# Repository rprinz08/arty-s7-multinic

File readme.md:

# Arty-S7-50, VexRiscV, Migen, LiteX, MulitNet

This project describes how to build a soft-core RiscV based system with multiple
Ethernet interfaces on a Digilent Arty-S7-50 with a Xilinx Spartan 7 FPGA using
Python based Migen HDL and LiteX SoC builder.

Prototype of the project

More evolved version with up to four Ethernet interfaces and a PCB. The [KiCad](https://kicad-pcb.org/) project files are included in this repository.

Download schematic as [PDF](doc/arty_s7_50_multi_net_sch.pdf).

It uses multiple [Texas Instruments DP83848](http://www.ti.com/product/DP83848-EP)
based RMII Ethernet PHYs from [Waveshare](https://www.waveshare.com/dp83848-ethernet-board.htm).
In addition a [SD-Card PMOD](https://store.digilentinc.com/pmod-microsd-microsd-card-slot/) completes the system.

Note: in the PCB version the Seven Segment Display was removed due to I/O limitations.

More infos about this project can be found in the accompanying blog posts
[here](https://www.min.at/prinz/?x=entry:entry200428-150015) and [here](https://www.min.at/prinz/?x=entry:entry200602-105212).

## Prerequisites

To build the FPGA bitstream, the SoC BIOS and the sample bare metal demo
application you need some prerequisites installed:

* [Xilinx Vivado](https://www.xilinx.com/products/design-tools/vivado.html)
* [Python >= 3.6](https://www.python.org/)
* [LiteX](https://github.com/enjoy-digital/litex)
  * Tested with git version (bddb170)
* [Liteeth](https://github.com/enjoy-digital/liteeth)
  * Tested with git version (dea3590)
* [RiscV compiler toolchain](https://static.dev.sifive.com/dev-tools/riscv64-unknown-elf-gcc-8.1.0-2019.01.0-x86_64-linux-ubuntu14.tar.gz)
* [OpenOCD](http://openocd.org/)
* [xc3sprog](https://sourceforge.net/projects/xc3sprog/) (optional)

*Note: As of LiteX version (bddb170) and Liteeth version (dea3590) no patches are needed for multiple ethernet support. If you use an older version you can find patches in the history.*

## Building

The included `make.py` script is responsible for building and loading/flashing.
In addition a `Makefile` is used to handle dependencies and file changes.
Assuming that all prerequisites are correctly installed using make:
```
make                Builds FPGA bitstream and BIOS software
make build-sw       Builds BIOS
make build-fpga     Builds FPGA bitstream
make conv           Convert Python FHDL to Verilog
make load           Loads bitstream into FPGA via serial port
make load-sw        Loads firmware binary using serial port
make reload         Same as "load" but does not rebuild in case of changes
make flash          Stores bitstream into FPGA boot flash
make flash-sw       Flash BIOS software
make reflash        Same as "flash" but does not rebuild in case of changes
make term           Opens LiteX serial lxterm console
make clean          Cleans/removes all build artefacts
```
The `make.py` script is called from make (Makefile) and provides the following:
```
make.py --help      shows basic help
make.py build       converts LiteX/Migen FHDL into verilog,
                    starts Xilinx Vivado and generates FPGA bitstream
make.py build-sw    same as 'build' but only builds BIOS
make.py build-fpga  same as 'build' but only builds FPGA bitstream
make.py load        loads the bitstream into FPGA
make.py flash       flashes the bitstream into config flash
make.py flash-sw    flashes the BIOS into config flash
make.py conv        creates all artefacts (verilog, c sources etc.)
                    but does not compile
```
In addition to the FPGA bitstream (which also includes the BIOS) a sample
application is included in the `firmware` directory. It can be compiled with
the included Makefile. The resulting `firmware.bin` can be loaded from SD-Card
or via TFTP from a server.

To load from SD-Card create a FAT16 partition on it and place `firmware.bin`
renamed to `boot.bin` in the root directory.

To load from TFTP server connect Ethernet interface 1 to a switch or directly
to a host via a cros-over network cable. Interface 1 is per default configured
with IP4 address **10.0.0.50** and tries to load from TFTP server with address
**10.0.0.100**. These addresses are static and can only be changed by modifying
`top.py` and re-building.
Place `firmware.bin` renamed to `BOOT.BIN` in the root directory of the TFTP
server.

To preserve the limited I/Os of the Arty the SD-Card can be removed and the
firmware booted from the SPI flash. The Arty has 16MB SPI flash normally used
to configure the FPGA with a bitstream at boot.
As lang as bitstream size + firmware size < 15MB they can reside together in
the flash. Current configuration halfs the flash. First half used for the
bitsream second half for the firmware. The `make flash-sw` writes the
`firmware.fbi` to flash adress 0x800000.

*Note: Due to BIOS ROM size limitations the option to boot from SPI flash has been disabled. Booting the system is possible via SPI SD-Card, TFTP and serial.*

## Running

Build and flash the FPGA bitstream:
```
make
make flash
```
To boot from SD-Card place `firmware.bin` renamed to `BOOT.BIN` on SD-Card and
reset the board. To boot from SPI flash, flash with `make flash-sw`.
On an attached serial terminal (open one with `make term`) you should see the
following output:
```
[LXTERM] Starting...
        __   _ __      _  __
       / /  (_) /____ | |/_/
      / /__/ / __/ -_)>  <
     /____/_/\__/\__/_/|_|
   Build your hardware, easily!

 (c) Copyright 2012-2020 Enjoy-Digital
 (c) Copyright 2007-2015 M-Labs

 BIOS built on May  1 2020 22:04:43
 BIOS CRC passed (f662f7bd)

 Migen git sha1: --------
 LiteX git sha1: 56aa7897

--=============== SoC ==================--
CPU:       VexRiscv @ 100MHz
ROM:       32KB
SRAM:      4KB
L2:        8KB
MAIN-RAM:  262144KB

--========== Initialization ============--
Ethernet init...
Initializing SDRAM...
SDRAM now under software control
Read leveling:
m0, b0: |00000000000000000000000000000000| delays: -
m0, b1: |00000000000000000000000000000000| delays: -
m0, b2: |00000000000000000000000000000000| delays: -
m0, b3: |00000000000000000000000000000000| delays: -
m0, b4: |00000000000000000000000000000000| delays: -
m0, b5: |00000000000000000000000000000000| delays: -
m0, b6: |00001111111111111000000000000000| delays: 10+-06
m0, b7: |00000000000000000000000000000000| delays: -
best: m0, b6 delays: 10+-06
m1, b0: |00000000000000000000000000000000| delays: -
m1, b1: |00000000000000000000000000000000| delays: -
m1, b2: |00000000000000000000000000000000| delays: -
m1, b3: |00000000000000000000000000000000| delays: -
m1, b4: |00000000000000000000000000000000| delays: -
m1, b5: |10000000000000000000000000000000| delays: 00+-00
m1, b6: |00001111111111111000000000000000| delays: 10+-06
m1, b7: |00000000000000000000000000000000| delays: -
best: m1, b6 delays: 10+-06
SDRAM now under hardware control
Memtest OK
Memspeed Writes: 262Mbps Reads: 327Mbps

--============== Boot ==================--
Booting from serial...
Press Q or ESC to abort boot completely.
sL5DdSMmkekro
Timeout
SD Card via SPI Initialising
Reading MBR
Partition 1 Information: Active=0x00, Type=0x06, LBAStart=0x00000800
Partition 1 is FAT16

Read FAT16 Boot Sector
  Jump Code:              0xeb 0x3c 0x90
  OEM Code:               [mkfs.fat]
  Sector Size:            512
  Sectors Per Cluster:    128
  Reserved Sectors:       128
  Number of Fats:         2
  Root Dir Entries:       2048
  Total Sectors Short:    0
  Media Descriptor:       0xf8
  Fat Size Sectors:       128
  Sectors Per Track:      32
  Number of Heads:        64
  Hidden Sectors:         2048
  Total Sectors Long:     4194304
  Drive Number:           0x80
  Current Head:           0x01
  Boot Signature:         0x29
  Volume ID:              0x3fab9b48
  Volume Label:           [LITEX      ]
  Volume Label:           [FAT16   ]
  Boot Sector Signature:  0xaa55

Reclocking from 400KHz to 14285KHz

sdCardFatTable = 0x4fff0000  Reading Fat16 Table (128 Sectors Long)

sdCardFat16RootDir = 0x4ffe0000  Reading Root Directory (128 Sectors Long)

Root Directory
  File 1 [BOOT    .BIN] @ Cluster 3 for 9532 bytes

Reading File [BOOT.BIN] into 0x40000000 : File starts at Cluster 3 length 9532
Clusters: 3

Executing booted program at 0x40000000

--============= Liftoff! ===============--
Hello firmware booting...

HELLO>
```

## Debugging

A [Litescope](https://github.com/enjoy-digital/litescope) debugger is available via eth2 with configured IP address of **10.0.0.42**. The `debug` directory contains some scripts and samples on how to use it.

## Firmware

After board reset the embedded BIOS is started which performs some basic
initalization and then tries to load the firmware via available peripherals.
In this case first via serial port, then via SD-Card and last via Ethernet.
It found the BOOT.BIN `hello` firmware on the SD-Card and loads it.

```
HELLO >help

Available commands:
hello value      - Returns value xor'ed with 0xff in FPGA
time             - show current clock ticks
uptime           - show system uptime in seconds
random [runs]    - show random number generator values, default [500] runs
malloc [runs]    - test UMM malloc, default [500] runs
ping             - ping host (10.0.0.100) via network interface (eth0)
reboot           - reboot CPU
help             - this command
```

The `hello` firmware just shows how to develop bare metal applications using
console in- and output and accessing FPGA logic blocks. Details about the firmware can be found [here](doc/firmware.md).

## RMII notes

Although there exists a OSCIN pin on the DP83848 PHY module which
suggests a clock input, it is the output of the 50MHz oscillator
available on the module. This oscillator directly clocks the DP83848
PHY and is available on the module connector as reference clock
output.

The default LiteX Liteeth RMII MAC operates with the clock of a 50MHz
PLL it instantiates assuming that it must provide the clock to the
PHY. As the PHY modules use their own oscillator the corresponding clock pads are set to Null in the code so that the external clock will be used.

To synchronize the MAC with the PHY the PHYs clock can be
used as input to the MAC instead of the default 50MHz PLL clock
output. 

On Xilinx Spartan7 FPGAs only the positive (P) version of clock
capable (CC) pins can be used as they are internally special wired
and there is only a limited number per I/O bank available.
As each module has its own oscillator they should be synced to its
corresponding MAC. This is somehow inefficient as normally multiple PHYs and
MACs share a common clock. But to prevent modifying each module, each modules
OSCIN is connected to one of four CC-P pin on
the FPGA syncing its corresponding MAC.

Although a simple modification on the module makes it possible to
share clocks. Removing the 0 Ohm resistor R1 makes it possible to clock the
modules from outside via the OSCIN pin.

More infos about this project can be found in the accompanying blog posts
[here](https://www.min.at/prinz/?x=entry:entry200428-150015) and [here](https://www.min.at/prinz/?x=entry:entry200602-105212).

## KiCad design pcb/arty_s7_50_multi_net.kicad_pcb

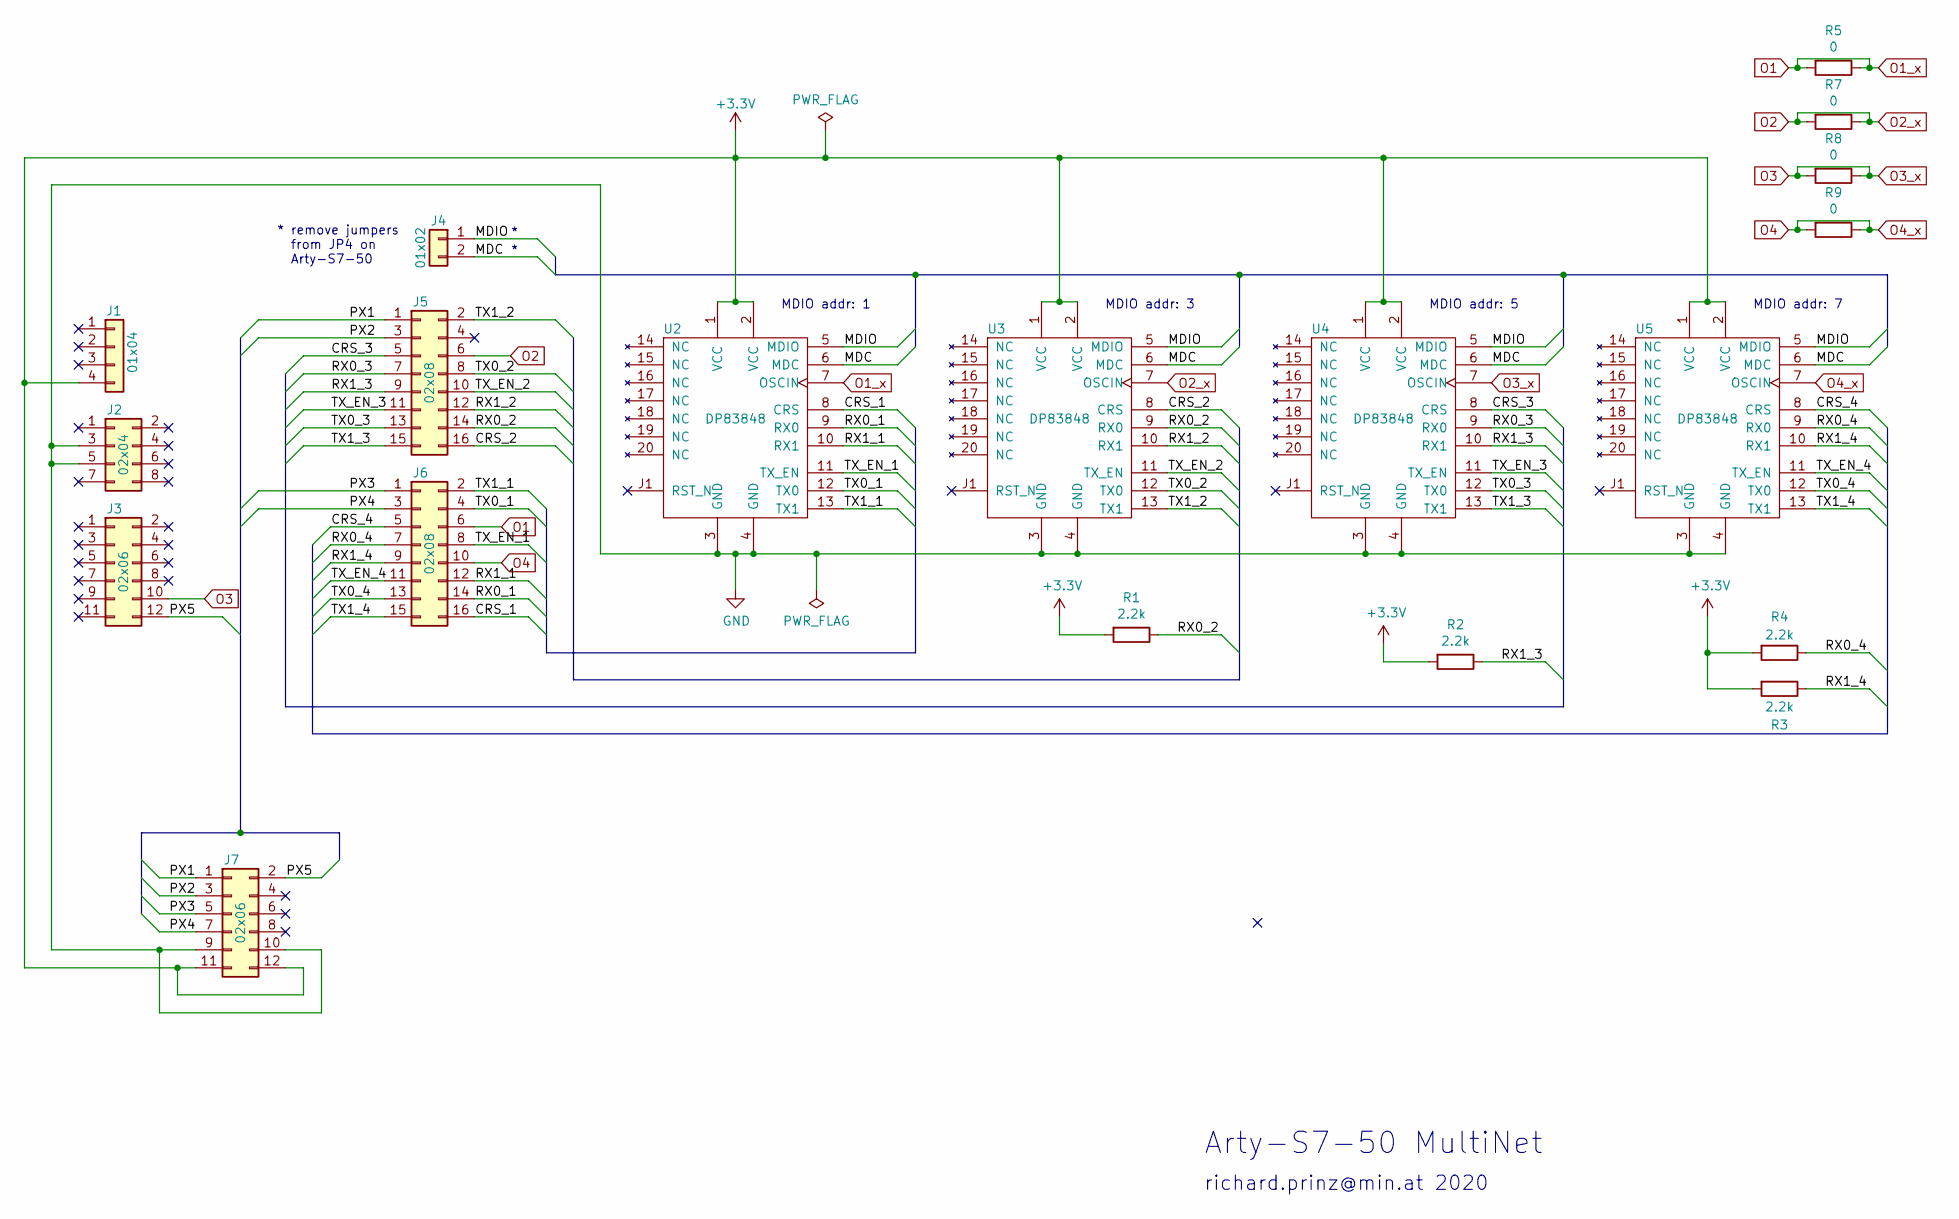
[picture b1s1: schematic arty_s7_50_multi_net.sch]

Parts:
J1: 01x04; Pin_Header_Straight_1x04_Pitch2.54mm
J2: 02x04; Pin_Header_Straight_2x04_Pitch2.54mm
J3, J7: 02x06; Pin_Header_Straight_2x06_Pitch2.54mm
J4: 01x02; Pin_Header_Straight_1x02_Pitch2.54mm
J5, J6: 02x08; Pin_Header_Straight_2x08_Pitch2.54mm
R1, R2, R3, R4: 2.2k; R_0805_HandSoldering
R5, R7, R8, R9: 0; R_0805_HandSoldering
U2, U3, U4, U5: DP83848; Socket_Strip_Straight_2x10_Pitch2.54mm

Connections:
+3V3: J1.4, J7.11, J7.12, R1.2, R2.2, R3.2, R4.2, U2.1 (VCC), U2.2 (VCC), U3.1 (VCC), U3.2 (VCC), U4.1 (VCC), U4.2 (VCC), U5.1 (VCC), U5.2 (VCC)
/CRS_1: J6.16, U2.8 (CRS)
/CRS_2: J5.16, U3.8 (CRS)
/CRS_3: J5.5, U4.8 (CRS)
/CRS_4: J6.5, U5.8 (CRS)
/MDC: J4.2, U2.6 (MDC), U3.6 (MDC), U4.6 (MDC), U5.6 (MDC)
/MDIO: J4.1, U2.5 (MDIO), U3.5 (MDIO), U4.5 (MDIO), U5.5 (MDIO)
/PX1: J5.1, J7.1
/PX2: J5.3, J7.3
/PX3: J6.1, J7.5
/PX4: J6.3, J7.7
/PX5: J3.12, J7.2
/RX0_1: J6.14, U2.9 (RX0)
/RX0_2: J5.14, R1.1, U3.9 (RX0)
/RX0_3: J5.7, U4.9 (RX0)
/RX0_4: J6.7, R4.1, U5.9 (RX0)
/RX1_1: J6.12, U2.10 (RX1)
/RX1_2: J5.12, U3.10 (RX1)
/RX1_3: J5.9, R2.1, U4.10 (RX1)
/RX1_4: J6.9, R3.1, U5.10 (RX1)
/TX0_1: J6.4, U2.12 (TX0)
/TX0_2: J5.8, U3.12 (TX0)
/TX0_3: J5.13, U4.12 (TX0)
/TX0_4: J6.13, U5.12 (TX0)
/TX1_1: J6.2, U2.13 (TX1)
/TX1_2: J5.2, U3.13 (TX1)
/TX1_3: J5.15, U4.13 (TX1)
/TX1_4: J6.15, U5.13 (TX1)
/TX_EN_1: J6.8, U2.11 (TX_EN)
/TX_EN_2: J5.10, U3.11 (TX_EN)
/TX_EN_3: J5.11, U4.11 (TX_EN)
/TX_EN_4: J6.11, U5.11 (TX_EN)
GND: J2.3, J2.5, J7.9, J7.10, U2.3 (GND), U2.4 (GND), U2.19 (NC), U2.20 (NC), U3.3 (GND), U3.4 (GND), U3.19 (NC), U3.20 (NC), U4.3 (GND), U4.4 (GND), U4.19 (NC), U4.20 (NC), U5.3 (GND), U5.4 (GND), U5.19 (NC), U5.20 (NC)
O1: J6.6, R5.1, R5.2, U2.7 (OSCIN)
O2: J5.6, R7.1, R7.2, U3.7 (OSCIN)
O3: J3.10, R8.1, R8.2, U4.7 (OSCIN)
O4: J6.10, R9.1, R9.2, U5.7 (OSCIN)

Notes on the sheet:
* remove jumpers from JP4 on Arty-S7-50
Arty-S7-50 MultiNet
richard.prinz@min.at 2020
MDIO addr: 1
MDIO addr: 3
MDIO addr: 5
MDIO addr: 7

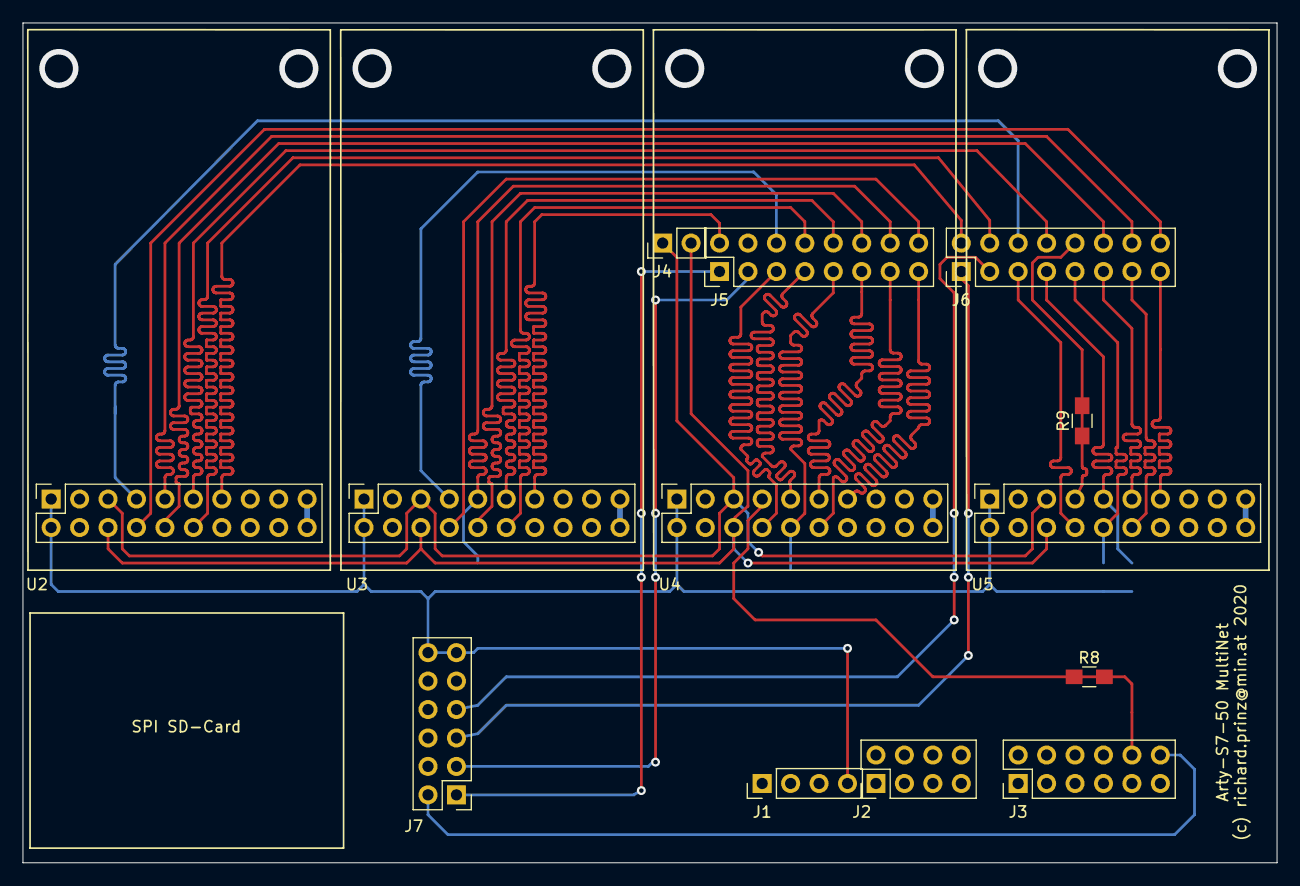
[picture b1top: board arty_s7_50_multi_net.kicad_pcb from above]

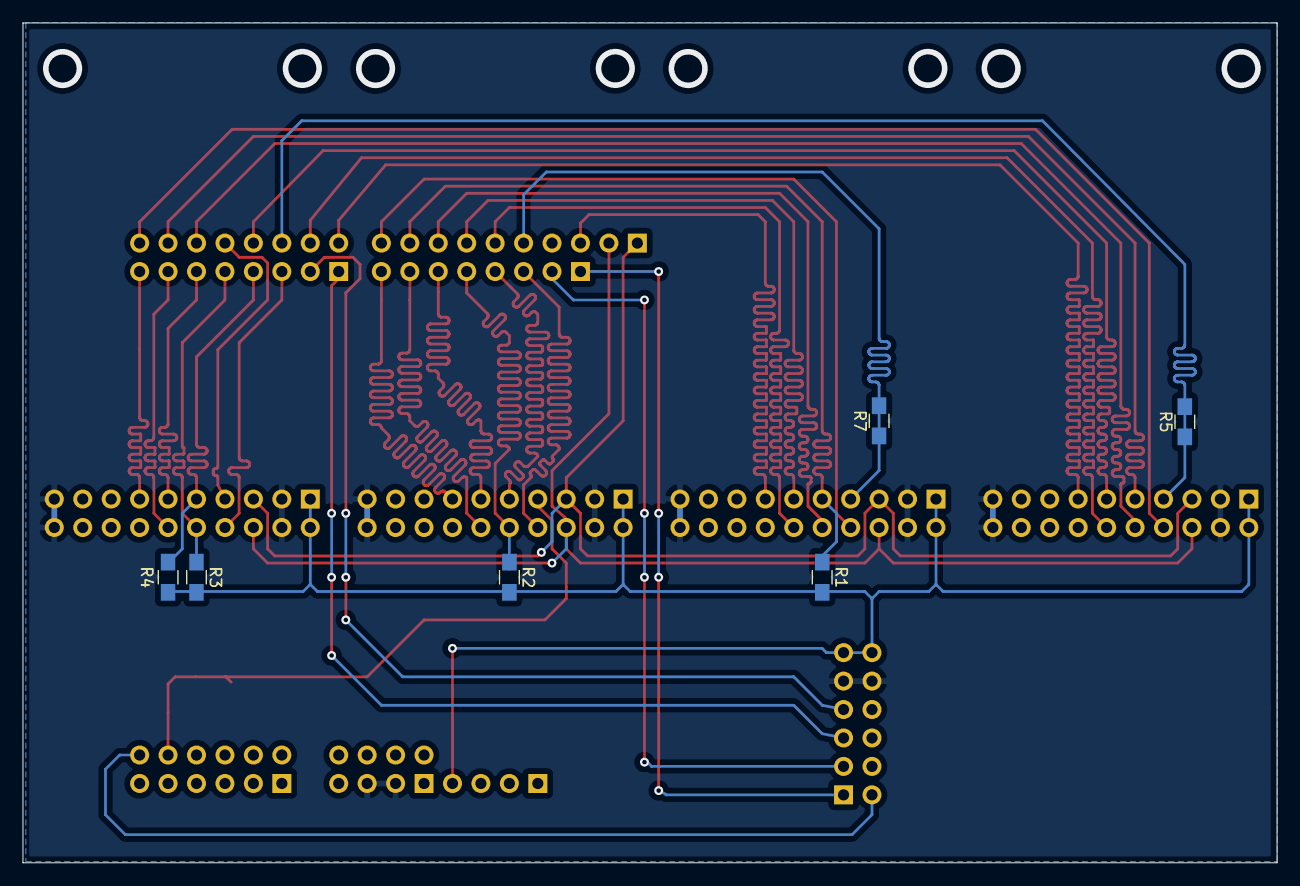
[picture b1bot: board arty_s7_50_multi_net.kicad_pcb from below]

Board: 2 copper layers, 112.0 x 75.0 mm, 19 parts (6 on the bottom side), 37 nets.

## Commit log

2020-05-06 modifications to support latest LiteX
2020-05-09 Added OpenOCD and booting firmware from SPI flash
2020-05-09 fixed typos
2020-05-12 Fixed boot from SPI flash
2020-05-15 Restructure project
2020-05-15 Remove unused signals
2020-05-15 Update documentation
2020-05-18 clock sync
2020-05-18 fixed typo
2020-05-27 Update for latest LiteX
2020-06-02 added KiCad PCB files
2020-06-03 Project clean-up
2020-06-05 Add liteeth patch
2020-06-06 Create LICENSE
2020-06-12 added ticker and timing functions to gate- and firm-ware
2020-06-12 added LFSR based PRNG using PRBS31
2020-06-12 Added UMM memory manager
2020-06-17 Added PicoTCP network stack
2020-06-22 fix typos
2020-06-29 fix for latest LiteX and SD-Card
2020-11-01 Fixes to support latest LiteX
2020-12-11 support latest LiteX git version
2020-12-11 added Litescope support
2020-12-11 typo and style fixes
2020-12-11 remove dead code
2020-12-22 Add support for latest LiteX
2020-12-22 Fix typo
2020-12-22 Fixed patch file
2020-12-23 Latest LiteX and Liteeth no longer require patches - removed them
